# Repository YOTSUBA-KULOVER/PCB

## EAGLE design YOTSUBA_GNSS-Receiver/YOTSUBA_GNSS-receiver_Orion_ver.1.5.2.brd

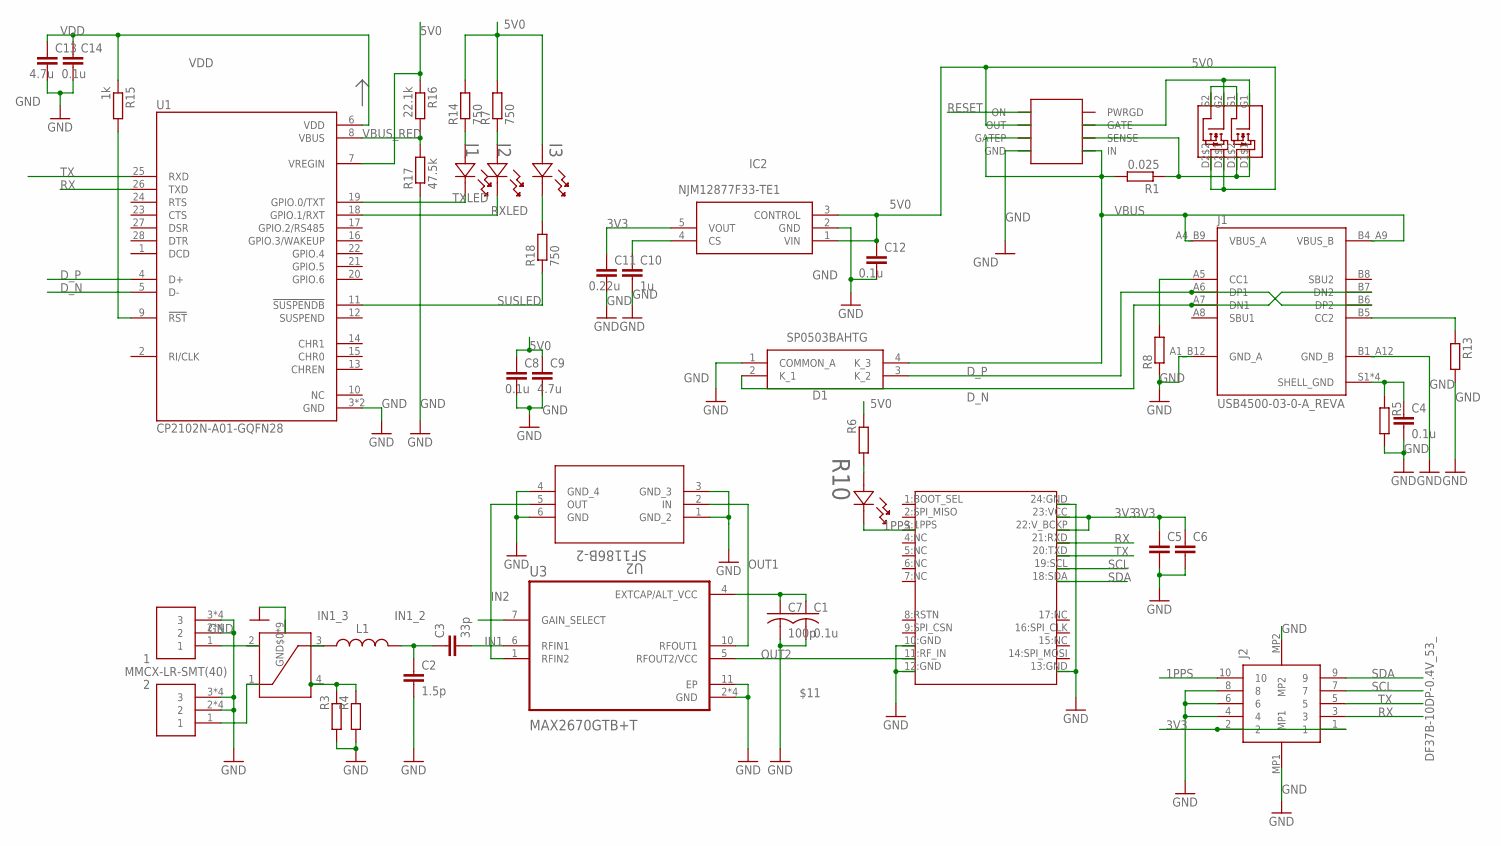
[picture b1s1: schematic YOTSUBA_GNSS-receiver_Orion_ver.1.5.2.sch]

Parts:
1, 2: MMCX-LR-SMT(40)
C1: 0.1u; C1608_OS
C2: 1.5p; C1608
C3: 33p; C1608
C4, C8, C12, C14: 0.1u; C1608
C5, C6: C-EUC1608; C1608
C7: 100p; C1608_OS
C9, C13: 4.7u; C1608
C10: 1u; C1608
C11: 0.22u; C1608
D1: SP0503BAHTG
I1, I2, I3: SML-E12P8WT86; LED_SMLD12_ROM
IC2: NJM12877F33-TE1; SOT95P280X120-5N
J1: USB4500-03-0-A_REVA; GCT_USB4500-03-0-A_REVA
J2: DF37B-10DP-0.4V_53_; DF37B10DP04V53
L1: LQW18AN4N3C00D; INDC1608X100N
R1: 0.025; R0603
R3, R4, R5, R6, R8, R13: R-EU_R0603; R0603
R7, R14, R18: 750; R0603
R10: SML-E12P8WT86; LED_SMLD12_ROM
R15: 1k; R0603
R16: 22.1k; R0603
R17: 47.5k; R0603
U1: CP2102N-A01-GQFN28; QFN50P500X500X80-29N
U2: SF1186B-2; SM3030_MUR
U3: MAX2670GTB+T; DFN300X300X80-11N
U$1: ORION_B16
U$3: HC125.A
U$7: DMG6898LSD; SOIC127P600X150-8N
U$8: LTC4361; SOP65P280X100-8N

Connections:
1PPS: J2.10, R10.1, U$1.3:1PPS
3V3: C5.1, C6.1, C11.1, IC2.5 (VOUT), J2.1, J2.2, U$1.22:V_BCKP, U$1.23:VCC
5V0: C8.1, C9.1, C12.1, I3.2, IC2.1 (VIN), IC2.3 (CONTROL), R6.2, R7.2, R14.2, R16.1, U1.7 (VREGIN), U$7.D2$1, U$7.D2$2, U$8.OUT
$11: C1.1, C7.1, U3.4 (EXTCAP/ALT_VCC)
D_N: D1.2 (K_1), J1.A7 (DN1), J1.B7 (DN2), U1.5 (D-)
D_P: D1.3 (K_2), J1.A6 (DP1), J1.B6 (DP2), U1.4 (D+)
GND: 1.2, 1.3, 1.4 (2), 1.5 (3), 1.P$1 (2), 1.P$2 (2), 1.P$3 (3), 1.P$4 (3), 2.2, 2.3, 2.4 (2), 2.5 (3), 2.P$1 (2), 2.P$2 (2), 2.P$3 (3), 2.P$4 (3), C1.2, C2.2, C4.2, C5.2, C6.2, C7.2, C8.2, C9.2, C10.2, C11.2, C12.2, C13.2, C14.2, D1.1 (COMMON_A), IC2.2 (GND), J1.A1_B12 (GND_A), J1.B1_A12 (GND_B), J2.4, J2.6, J2.8, J2.MP1, J2.MP2, R3.1, R4.1, R5.2, R8.1, R13.2, R17.1, U1.3 (GND), U1.29 (GND), U2.1 (GND_2), U2.3 (GND_3), U2.4 (GND_4), U2.6 (GND), U3.2 (GND), U3.3 (GND), U3.8 (GND), U3.9 (GND), U3.11 (EP), U$1.10:GND, U$1.12:GND, U$1.13:GND, U$1.24:GND, U$3.GND$0 (GND), U$3.GND$1 (GND), U$3.GND$2 (GND), U$3.GND$3 (GND), U$3.GND$4 (GND), U$3.GND$5 (GND), U$3.GND$6 (GND), U$3.GND$7 (GND), U$3.GND$8 (GND), U$8.GND
IN1: C3.2, U3.6 (RFIN1)
IN1_2: C2.1, C3.1, L1.2
IN1_3: L1.1, U$3.3
IN2: U2.5 (OUT), U3.1 (RFIN2)
unnamed: 1.1, U$3.2
unnamed: 2.1, U$3.1
unnamed: I3.1, R18.2
unnamed: C10.1, IC2.4 (CS)
unnamed: I2.2, R7.1
unnamed: C4.1, J1.S1 (SHELL_GND), J1.S2 (SHELL_GND), J1.S3 (SHELL_GND), J1.S4 (SHELL_GND), R5.1
unnamed: I1.2, R14.1
unnamed: R3.2, R4.2, U$3.4
unnamed: R6.1, R10.2
unnamed: U$7.S1, U$7.S2
unnamed: R1.1, U$7.D1$1, U$7.D1$2, U$8.SENSE
unnamed: J1.B5 (CC2), R13.1
unnamed: U$7.G1, U$7.G2, U$8.GATE
unnamed: J1.A5 (CC1), R8.2
unnamed: R15.2, U1.9 (!RST)
OUT1: U2.2 (IN), U3.10 (RFOUT1)
OUT2: U3.5 (RFOUT2/VCC), U$1.11:RF_IN
RESET: U$8.ON
RX: J2.3, U1.26 (TXD), U$1.21:RXD
RXLED: I2.1, U1.18 (GPIO.1/RXT)
SCL: J2.7, U$1.19:SCL
SDA: J2.9, U$1.18:SDA
SUSLED: R18.1, U1.11 (!SUSPENDB)
TX: J2.5, U1.25 (RXD), U$1.20:TXD
TXLED: I1.1, U1.19 (GPIO.0/TXT)
VBUS: D1.4 (K_3), J1.A4_B9 (VBUS_A), J1.B4_A9 (VBUS_B), R1.2, U$8.GATEP, U$8.IN
VBUS_RED: R16.2, R17.2, U1.8 (VBUS)
VDD: C13.1, C14.1, R15.1, U1.6 (VDD)

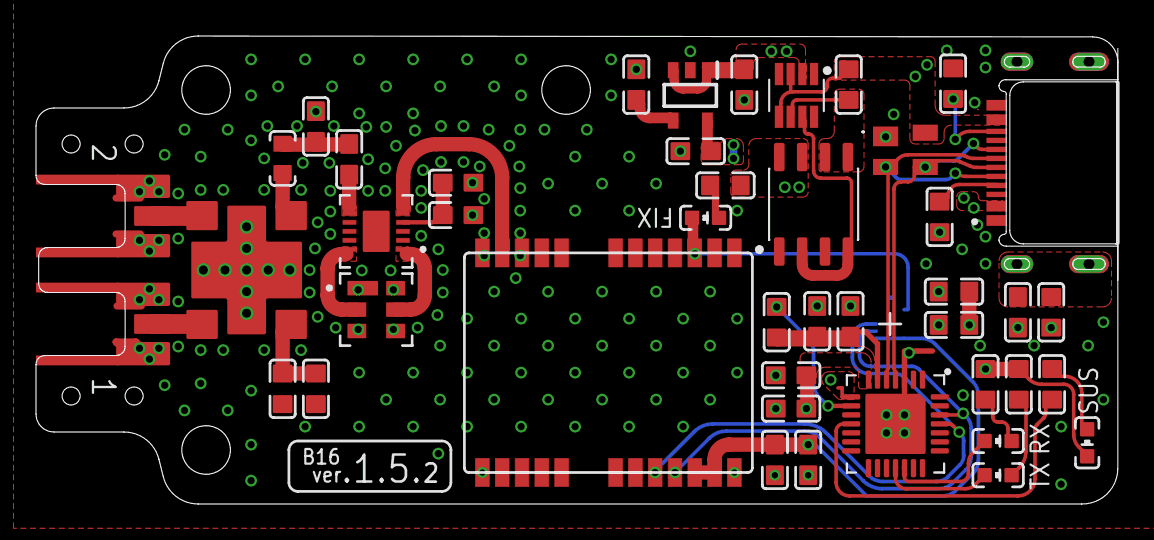
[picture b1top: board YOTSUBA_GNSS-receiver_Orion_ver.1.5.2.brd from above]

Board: 4 copper layers, 60.1 x 26.0 mm, 45 parts (1 on the bottom side), 38 nets.

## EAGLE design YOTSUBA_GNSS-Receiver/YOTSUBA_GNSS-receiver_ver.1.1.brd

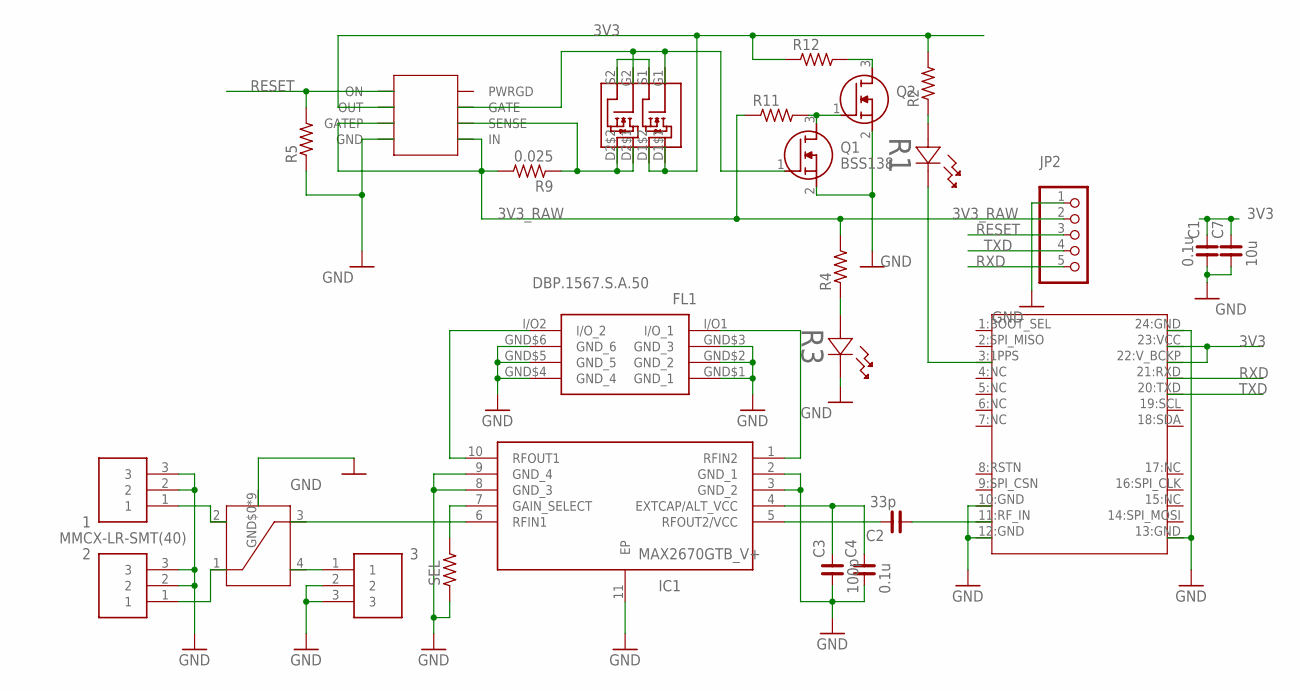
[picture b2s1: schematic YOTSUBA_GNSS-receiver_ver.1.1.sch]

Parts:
1, 2, 3: MMCX-LR-SMT(40)
C1, C4: 0.1u; C0603
C2: 33p; C0603
C3: 100p; C0603
C7: 10u; C0603
FL1: DBP.1567.S.A.50; DBP1567SA50
IC1: MAX2670GTB_V+; SON50P300X300X80-11N
JP2: PINHD-1X5; 1X05
Q1, Q2: BSS138; SOT95P240X120-3N
R1, R3: SML-E12P8WT86; LED_SMLD12_ROM
R2, R4, R5, R11, R12: R_0603; R0603
R9: 0.025; R0603
SEL: R_0603; R0603
U$1: ORION_B16
U$3: HC125.A
U$7: DMG6898LSD; SOIC127P600X150-8N
U$8: LTC4361; SOP65P280X100-8N

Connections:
3V3: C1.2, C7.2, R2.2, R12.1, U$1.22:V_BCKP, U$1.23:VCC, U$7.D1$1, U$7.D1$2, U$8.OUT
3V3_RAW: JP2.2, R4.2, R9.2, R11.1, U$8.GATEP, U$8.IN
GND: 1.2, 1.3, 2.2, 2.3, 3.2, 3.3, C1.1, C3.1, C4.1, C7.1, FL1.GND$1 (GND_1), FL1.GND$2 (GND_2), FL1.GND$3 (GND_3), FL1.GND$4 (GND_4), FL1.GND$5 (GND_5), FL1.GND$6 (GND_6), IC1.2 (GND_1), IC1.3 (GND_2), IC1.8 (GND_3), IC1.9 (GND_4), IC1.11 (EP), JP2.1, Q1.2 (S), Q2.2 (S), R3.1, R5.1, SEL.1, U$1.10:GND, U$1.12:GND, U$1.13:GND, U$1.24:GND, U$3.GND$0 (GND), U$3.GND$1 (GND), U$3.GND$2 (GND), U$3.GND$3 (GND), U$3.GND$4 (GND), U$3.GND$5 (GND), U$3.GND$6 (GND), U$3.GND$7 (GND), U$3.GND$8 (GND), U$8.GND
unnamed: 1.1, U$3.2
unnamed: 2.1, U$3.1
unnamed: IC1.6 (RFIN1), U$3.3
unnamed: R1.1, U$1.3:1PPS
unnamed: R1.2, R2.1
unnamed: 3.1, U$3.4
unnamed: IC1.7 (GAIN_SELECT), SEL.2
unnamed: FL1.I/O2 (I/O_2), IC1.10 (RFOUT1)
unnamed: FL1.I/O1 (I/O_1), IC1.1 (RFIN2)
unnamed: C3.2, C4.2, IC1.4 (EXTCAP/ALT_VCC)
unnamed: C2.2, IC1.5 (RFOUT2/VCC)
unnamed: C2.1, U$1.11:RF_IN
unnamed: R3.2, R4.1
unnamed: U$7.S1, U$7.S2
unnamed: R9.1, U$7.D2$1, U$7.D2$2, U$8.SENSE
unnamed: Q1.1 (G), U$7.G1, U$7.G2, U$8.GATE
unnamed: Q1.3 (D), Q2.1 (G), R11.2
unnamed: Q2.3 (D), R12.2
RESET: JP2.3, R5.2, U$8.ON
RXD: JP2.5, U$1.21:RXD
TXD: JP2.4, U$1.20:TXD

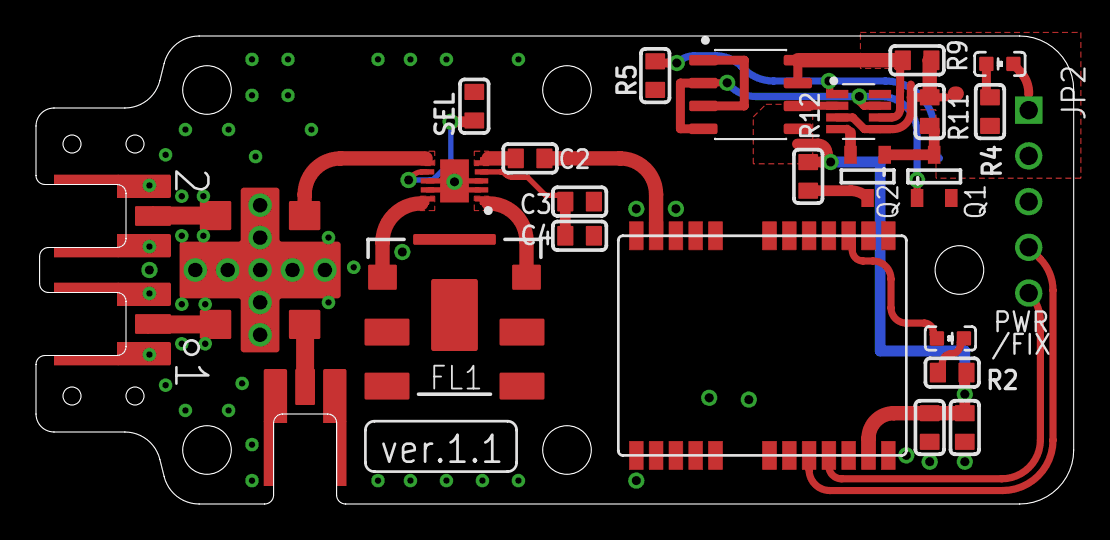
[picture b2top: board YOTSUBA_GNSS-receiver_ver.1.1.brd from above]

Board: 2 copper layers, 57.6 x 26.0 mm, 26 parts (0 on the bottom side), 24 nets.

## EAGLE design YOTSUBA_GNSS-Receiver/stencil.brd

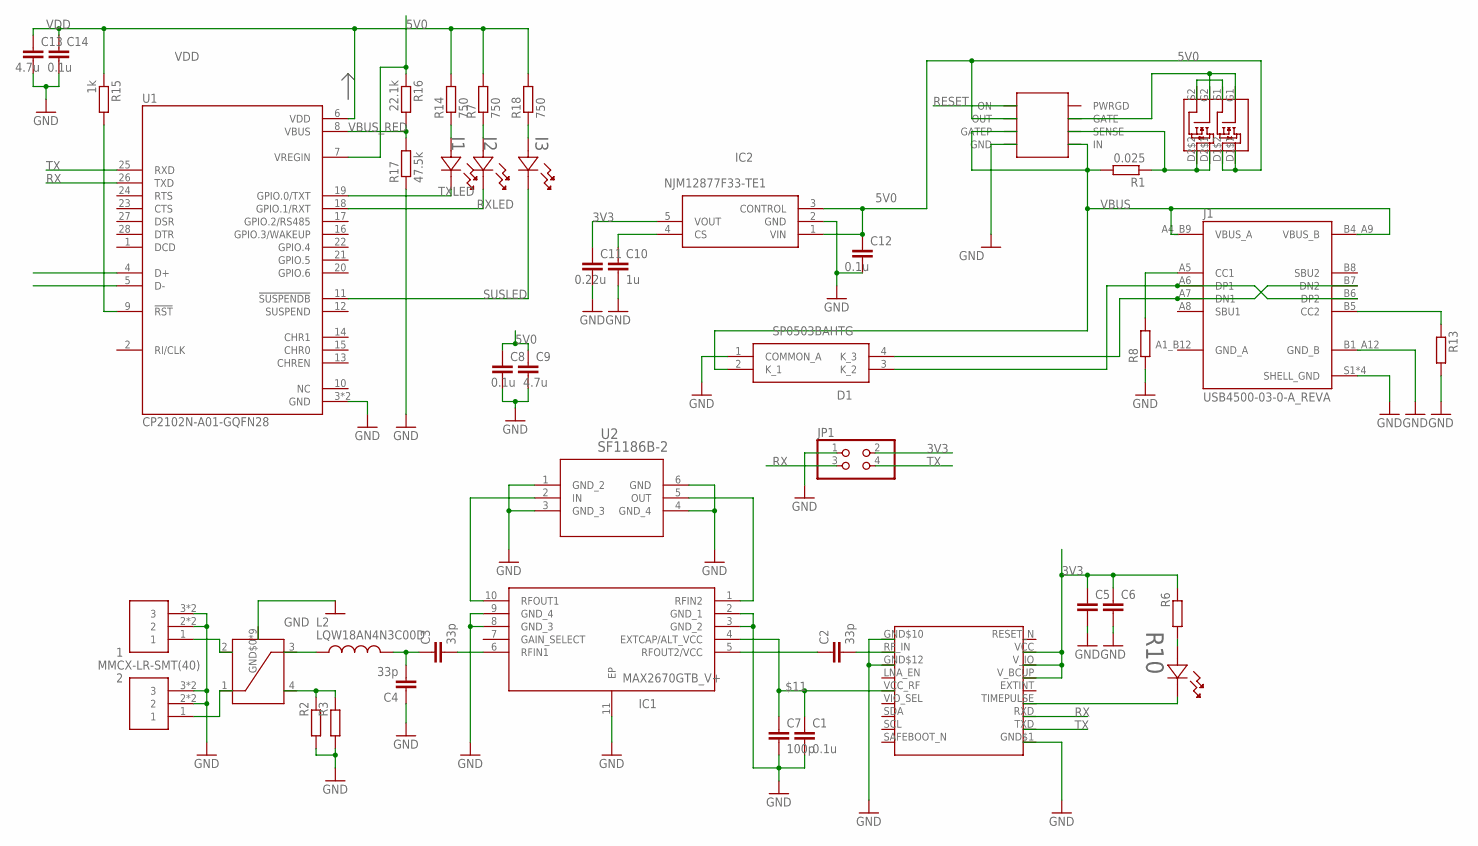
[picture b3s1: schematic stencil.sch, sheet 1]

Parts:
1, 2: MMCX-LR-SMT(40)
C1, C8, C12, C14: 0.1u; C1608
C2, C3, C4: 33p; C1608
C5, C6: C-EUC1608; C1608
C7: 100p; C1608
C9, C13: 4.7u; C1608
C10: 1u; C1608
C11: 0.22u; C1608
D1: SP0503BAHTG
I1, I2, I3: SML-E12P8WT86; LED_SMLD12_ROM
IC1: MAX2670GTB_V+; SON50P300X300X80-11N
IC2: NJM12877F33-TE1; SOT95P280X120-5N
J1: USB4500-03-0-A_REVA; GCT_USB4500-03-0-A_REVA
JP1: PINHD-2X2; 2X02
L2: LQW18AN4N3C00D; INDC1608X100N
R1: 0.025; R0603
R2, R3, R6, R8, R13: R-EU_R0603; R0603
R7, R14, R18: 750; R0603
R10: SML-E12P8WT86; LED_SMLD12_ROM
R15: 1k; R0603
R16: 22.1k; R0603
R17: 47.5k; R0603
U1: CP2102N-A01-GQFN28; QFN50P500X500X80-29N
U2: SF1186B-2; SM3030_MUR
U$1: MAX_M10S; MAX-M10S
U$3: HC125.A
U$7: DMG6898LSD; SOIC127P600X150-8N
U$8: LTC4361; SOP65P280X100-8N

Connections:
3V3: C5.1, C6.1, C11.1, IC2.5 (VOUT), JP1.2, R6.2, U$1.VCC, U$1.V_BCUP (V_BCKP), U$1.V_IO; also elsewhere on the board
5V0: C8.1, C9.1, C12.1, IC2.1 (VIN), IC2.3 (CONTROL), R16.1, U1.7 (VREGIN), U$7.D1$1, U$7.D1$2, U$8.OUT; also elsewhere on the board
$11: C1.1, C7.1, IC1.4 (EXTCAP/ALT_VCC), U$1.VCC_RF
D+: D1.3 (K_2), J1.A6 (DP1), J1.B6 (DP2), U1.4 (D+)
D-: D1.4 (K_3), J1.A7 (DN1), J1.B7 (DN2), U1.5 (D-)
GND: 1.2, 1.3, 1.4 (2), 1.5 (3), 2.2, 2.3, 2.4 (2), 2.5 (3), C1.2, C4.1, C5.2, C6.2, C7.2, C8.2, C9.2, C10.2, C11.2, C12.2, C13.2, C14.2, D1.1 (COMMON_A), IC1.2 (GND_1), IC1.3 (GND_2), IC1.8 (GND_3), IC1.9 (GND_4), IC1.11 (EP), IC2.2 (GND), J1.A1_B12 (GND_A), J1.B1_A12 (GND_B), J1.S1 (SHELL_GND), J1.S2 (SHELL_GND), J1.S3 (SHELL_GND), J1.S4 (SHELL_GND), JP1.1, R2.1, R3.1, R8.1, R13.2, R17.1, U1.3 (GND), U1.29 (GND), U2.1 (GND_2), U2.3 (GND_3), U2.4 (GND_4), U2.6 (GND), U$1.GND$1, U$1.GND$10, U$1.GND$12, U$3.GND$0 (GND), U$3.GND$1 (GND), U$3.GND$2 (GND), U$3.GND$3 (GND), U$3.GND$4 (GND), U$3.GND$5 (GND), U$3.GND$6 (GND), U$3.GND$7 (GND), U$3.GND$8 (GND), U$8.GND; also elsewhere on the board
unnamed: 1.1, U$3.2
unnamed: 2.1, U$3.1
unnamed: C10.1, IC2.4 (CS)
unnamed: I2.2, R7.1
unnamed: R2.2, R3.2, U$3.4
unnamed: L2.1, U$3.3
unnamed: IC1.10 (RFOUT1), U2.2 (IN)
unnamed: IC1.1 (RFIN2), U2.5 (OUT)
unnamed: C3.2, IC1.6 (RFIN1)
unnamed: C2.1, IC1.5 (RFOUT2/VCC)
unnamed: C2.2, U$1.RF_IN
unnamed: I1.2, R14.1
unnamed: R10.1, U$1.TIMEPULSE
unnamed: R6.1, R10.2
unnamed: I3.2, R18.1
unnamed: C3.1, C4.2, L2.2
unnamed: U$7.S1, U$7.S2
unnamed: R1.1, U$7.D2$1, U$7.D2$2, U$8.SENSE
unnamed: J1.B5 (CC2), R13.1
unnamed: U$7.G1, U$7.G2, U$8.GATE
unnamed: J1.A5 (CC1), R8.2
unnamed: R15.2, U1.9 (!RST)
RESET: U$8.ON
RX: JP1.3, U1.26 (TXD), U$1.RXD; also elsewhere on the board
RXLED: I2.1, U1.18 (GPIO.1/RXT)
SUSLED: I3.1, U1.11 (!SUSPENDB)
TX: JP1.4, U1.25 (RXD), U$1.TXD; also elsewhere on the board
TXLED: I1.1, U1.19 (GPIO.0/TXT)
VBUS: D1.2 (K_1), J1.A4_B9 (VBUS_A), J1.B4_A9 (VBUS_B), R1.2, U$8.GATEP, U$8.IN
VBUS_RED: R16.2, R17.2, U1.8 (VBUS)
VDD: C13.1, C14.1, R7.2, R14.2, R15.1, R18.2, U1.6 (VDD)

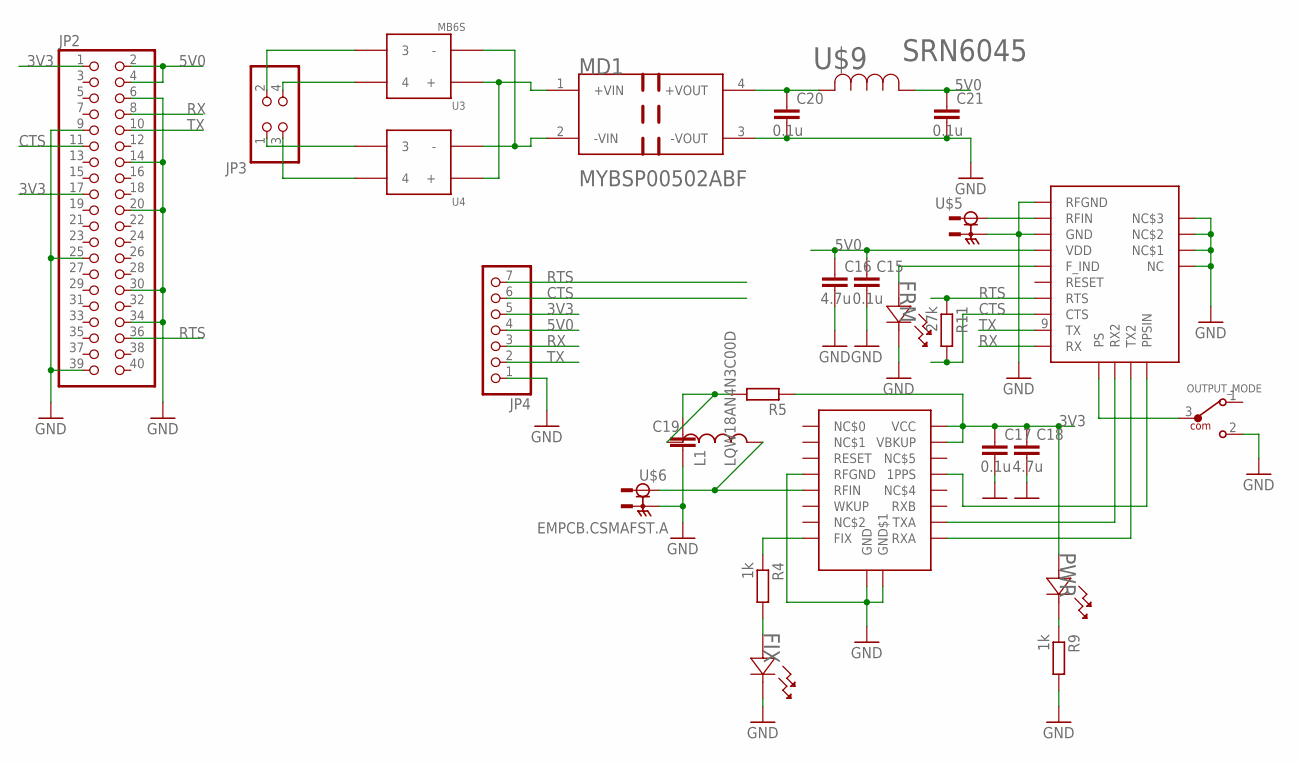
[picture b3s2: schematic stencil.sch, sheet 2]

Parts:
C15, C17, C20, C21: 0.1u; C1608
C16, C18: 4.7u; C1608
C19: C-EUC1608; C1608
FIX: SML-E12P8WT86; LED_SMLD12_ROM
FRM: SML-E12P8WT86; LED_SMLD12_ROM
JP2: PINHD-2X20; 2X20
JP3: PINHD-2X2; 2X02
JP4: PINHD-1X7/90; 1X07/90
L1: LQW18AN4N3C00D; INDC1608X100N
MD1: MURATA_MYBSP00502ABFMURATA_MYBSP00502ABF_0_0; MURATA_MYBSP00502ABF_0
OUTPUT_MODE: 450405020524
PWR: SML-E12P8WT86; LED_SMLD12_ROM
R4, R9: 1k; R0603
R5: R-EU_R0603; R0603
R11: 27k; R0603_NOSILK
U3, U4: MB6S; SOIC245P670X270-4N
U$2: GNS5894T; GNS5XXX
U$4: GNS3303
U$5, U$6: EMPCB.CSMAFST.A
U$9: SRN6045; IND_BOURNS_SRN6045

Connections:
3V3: C17.1, C18.1, JP2.1, JP2.17, JP4.5, PWR.2, R5.1, U$4.15 (VBKUP), U$4.16 (VCC); also elsewhere on the board
5V0: C15.1, C16.1, C21.1, JP2.2, JP2.4, JP4.4, U$2.4 (VDD), U$9.1; also elsewhere on the board
CTS: JP2.11, JP4.6, R11.2, U$2.8 (CTS)
GND: C15.2, C16.2, C17.2, C18.2, C19.2, C20.2, C21.2, FIX.1, FRM.1, JP2.6, JP2.9, JP2.14, JP2.20, JP2.25, JP2.30, JP2.34, JP2.39, JP4.1, MD1.3 (-VOUT), OUTPUT_MODE.2 (3), R9.2, U$2.1 (RFGND), U$2.3 (GND), U$2.15 (NC), U$2.16 (NC$1), U$2.17 (NC$2), U$2.18 (NC$3), U$4.4 (RFGND), U$4.E1 (GND), U$4.E2 (GND$1), U$5.GND$0 (2), U$5.GND$1 (2), U$5.GND$2 (2), U$5.GND$3 (2), U$6.GND$0 (2), U$6.GND$1 (2), U$6.GND$2 (2), U$6.GND$3 (2); also elsewhere on the board
unnamed: FRM.2, U$2.5 (F_IND)
unnamed: U$2.12 (RX2), U$4.10 (TXA)
unnamed: U$2.13 (TX2), U$4.9 (RXA)
unnamed: U$2.14 (PPSIN), U$4.13 (1PPS)
unnamed: R4.1, U$4.8 (FIX)
unnamed: FIX.2, R4.2
unnamed: C19.1, L1.1, R5.2
unnamed: OUTPUT_MODE.3 (2), U$2.11 (PS)
unnamed: PWR.1, R9.1
unnamed: JP3.4, U3.4
unnamed: JP3.2, U3.3
unnamed: JP3.3, U4.4
unnamed: JP3.1, U4.3
unnamed: MD1.2 (-VIN), U3.2 (-), U4.2 (-)
unnamed: MD1.1 (+VIN), U3.1 (+), U4.1 (+)
unnamed: C20.1, MD1.4 (+VOUT), U$9.2
RF1: L1.2, U$4.5 (RFIN), U$6.RF (1)
RF2: U$2.2 (RFIN), U$5.RF (1)
RTS: JP2.36, JP4.7, R11.1, U$2.7 (RTS)
RX: JP2.8, JP4.3, U$2.10 (RX); also elsewhere on the board
TX: JP2.10, JP4.2, U$2.9 (TX); also elsewhere on the board

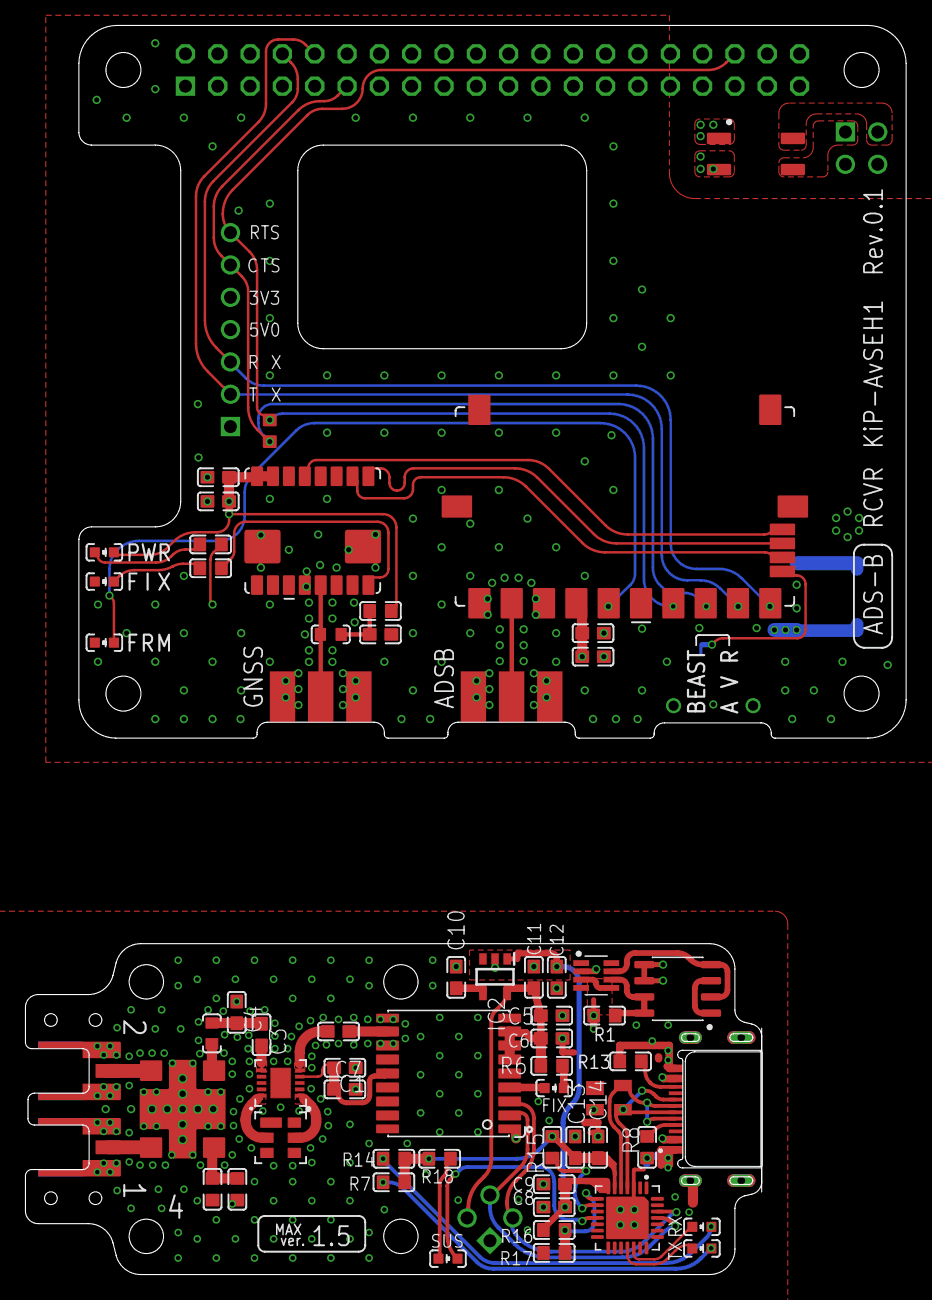
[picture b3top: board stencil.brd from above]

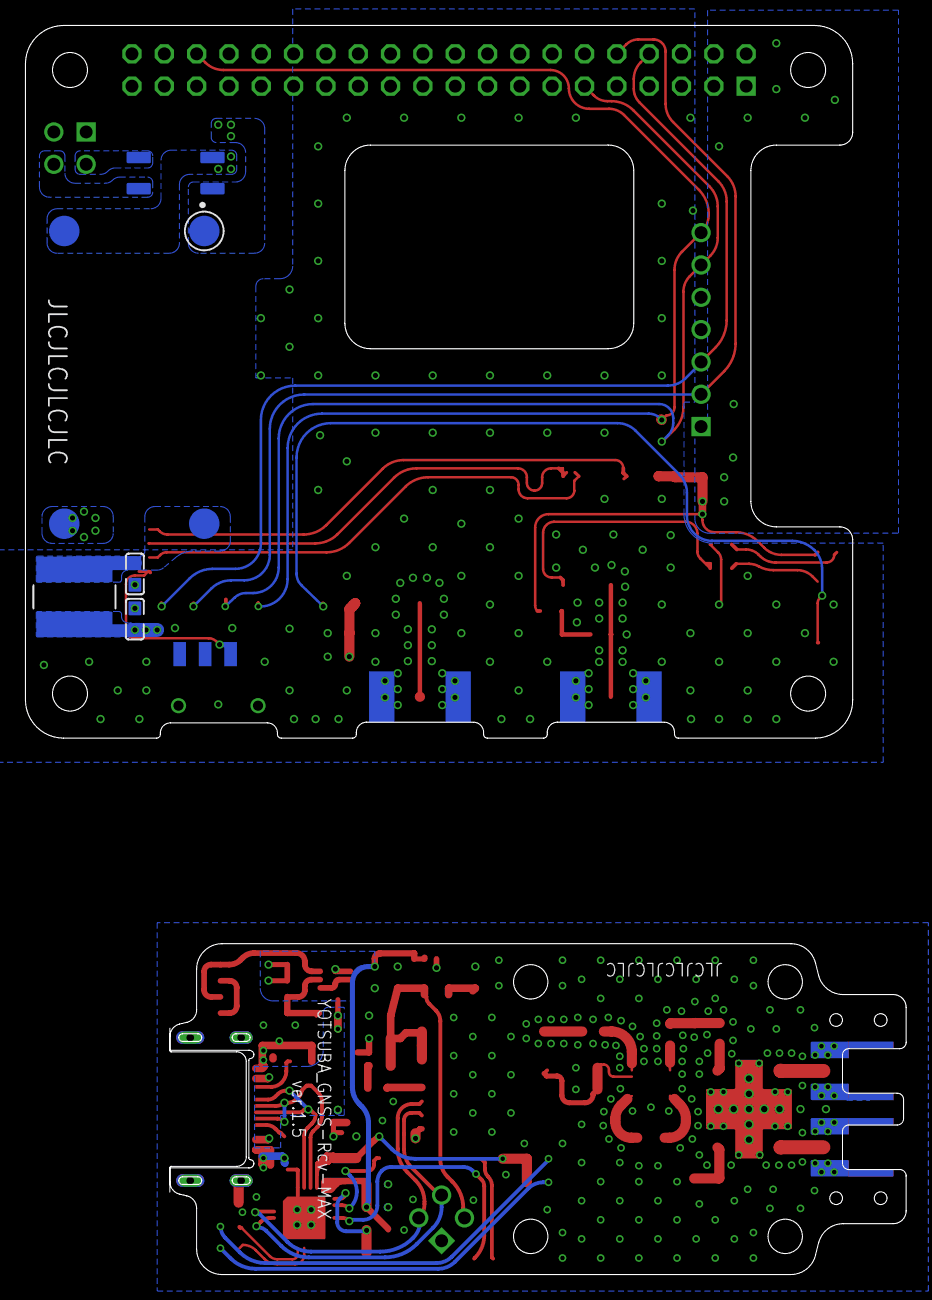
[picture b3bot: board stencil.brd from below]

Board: 2 copper layers, 69.2 x 98.2 mm, 71 parts (7 on the bottom side), 56 nets.

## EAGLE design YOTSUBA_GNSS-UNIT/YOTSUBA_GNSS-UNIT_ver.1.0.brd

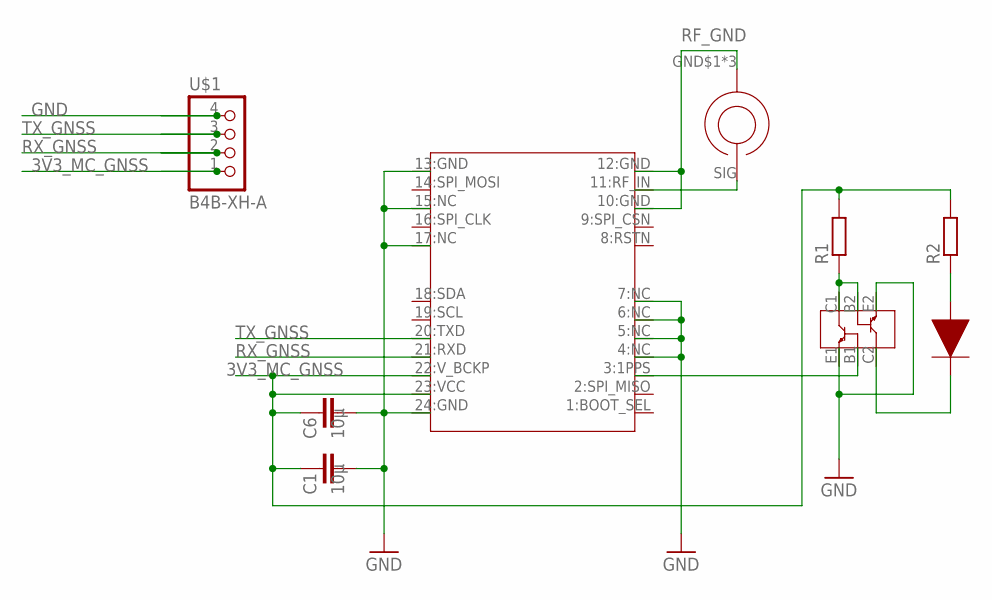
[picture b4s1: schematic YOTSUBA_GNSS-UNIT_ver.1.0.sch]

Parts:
C1, C6: 10μ; C2012
ON/1PPS: LED_1608
R1, R2: R-EU_M2012; M2012
U$1: B4B-XH-A
U$2: ORION_B16
U$3: HN1C01FU; SOT65P210X100-6N
U$5: U.FL-R

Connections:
3V3_MC_GNSS: C1.1, C6.1, R1.2, R2.2, U$1.1, U$2.22:V_BCKP, U$2.23:VCC
GND: C1.2, C6.2, U$1.4, U$2.4:NC, U$2.5:NC, U$2.6:NC, U$2.7:NC, U$2.13:GND, U$2.15:NC, U$2.17:NC, U$2.24:GND, U$3.E1, U$3.E2
unnamed: ON/1PPS.A, R2.1
unnamed: ON/1PPS.C, U$3.C2
unnamed: U$2.3:1PPS, U$3.B1
unnamed: R1.1, U$3.B2, U$3.C1
unnamed: U$2.11:RF_IN, U$5.SIG
RF_GND: U$2.10:GND, U$2.12:GND, U$5.GND$1 (GND), U$5.GND$2 (GND), U$5.GND$3 (GND)
RX_GNSS: U$1.2, U$2.21:RXD
TX_GNSS: U$1.3, U$2.20:TXD

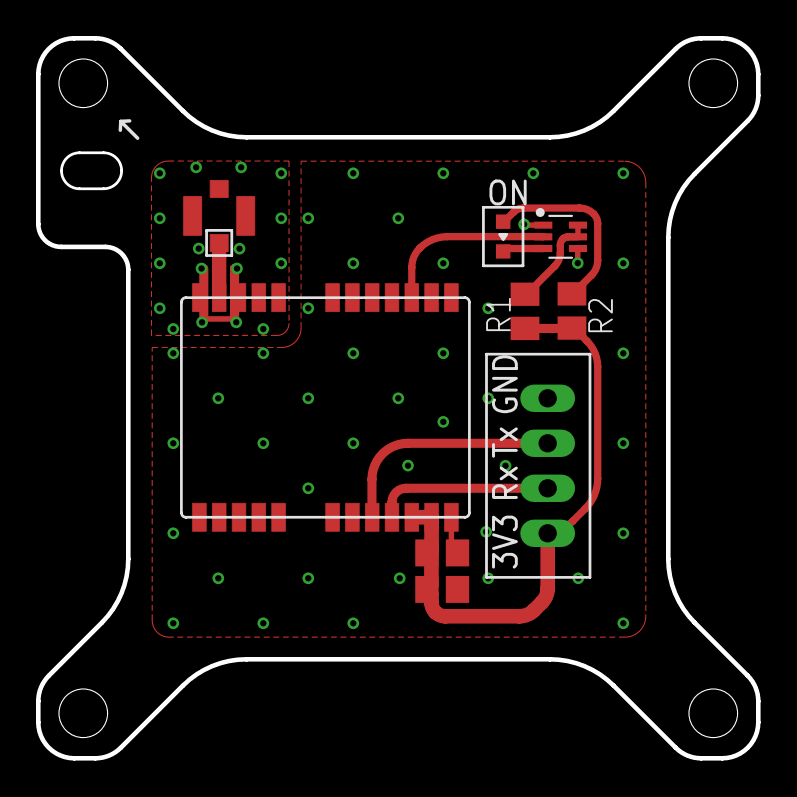
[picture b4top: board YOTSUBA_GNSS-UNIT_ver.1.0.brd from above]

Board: 2 copper layers, 40.0 x 40.0 mm, 9 parts (0 on the bottom side), 10 nets.

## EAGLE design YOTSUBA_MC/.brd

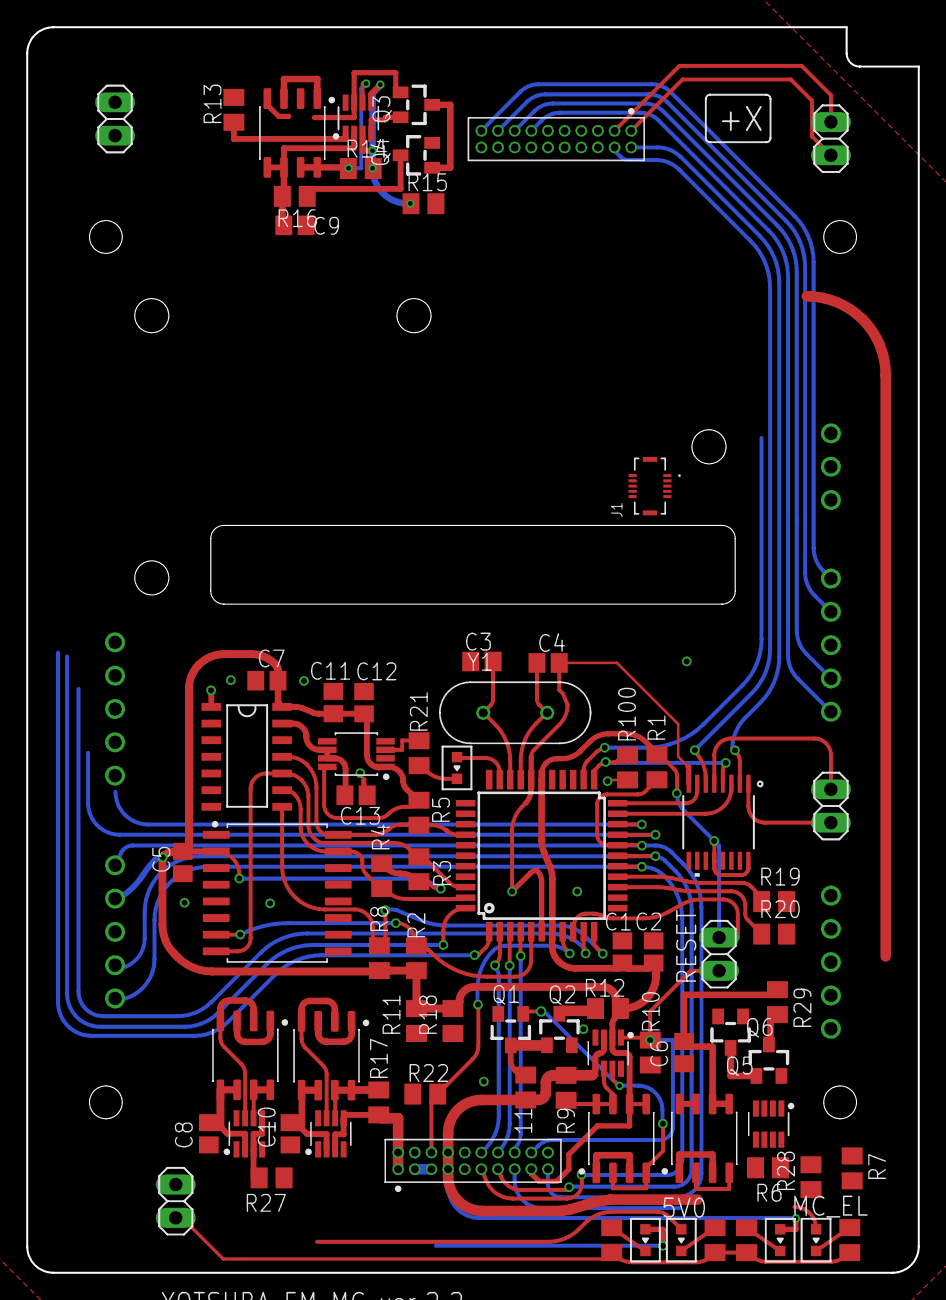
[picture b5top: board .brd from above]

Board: 2 copper layers, 68.0 x 95.0 mm, 84 parts (0 on the bottom side), 76 nets.

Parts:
11: M2012
C1, C2, C3, C4, C5, C6, C7, C8, C9, C10, C11, C12, C13: 10μ; C2012
COM_MAG: 1X05
J1: DF37NB-10DS-0.4V(51); HRS_DF37NB-10DS-0.4V(51)
JP1, JP4: 1X02
MAG_PWR: 1X03
PANEL: 1X05
PROGRAM: 1X05
Q1, Q2, Q3, Q4, Q5, Q6: BSS138; SOT23
R1, R2, R3, R4, R5, R6, R7, R8, R10, R11, R12, R13, R14, R15, R16, R17, R18, R19, R20, R21, R22, R23, R24, R25, R26, R27, R28, R29: M2012
R9: 0.025; M2012
R100: 100k; M2012
RPI: 1X05
U1: MAX4702EUE+; 21-0066J_16
U2: PIC16F877PT; TQFP44
U$1: MT25QL512_16SOP2; SOIC127P1032X265-16N
U$2, U$7, U$9, U$10, U$13: DMG6898LSD; SOIC127P600X150-8N
U$3, U$8, U$11, U$12, U$14: LTC4361; SOP65P280X100-8N
U$6: MCP3204_S
U$16, U$20, U$26: 1X02
U$17, U$22: M50-3001045
U$18, U$21, U$23, U$24, U$25: LED_1608
U$19: ADR35XX; SOP65P490X110-8N
Y1: HC-49/U-S16000000ABJB; XTAL_HC49P488W43L1150T466H350

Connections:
3V3: 11.1, MAG_PWR.1, R6.2, R9.2, R14.2, R15.1, R28.1, U$3.GATEP, U$3.IN, U$8.GATEP, U$8.IN, U$11.GATEP, U$11.IN, U$17.7, U$17.8, U$23.A
3V3_MAG: C6.2, R29.1, U$2.D1$1, U$2.D1$2, U$3.OUT
3V3_MC_EL: C1.1, C2.1, C5.2, C7.2, C11.2, C12.2, JP4.1, PROGRAM.2, R1.2, R2.2, R3.2, R4.2, R5.2, R8.1, R11.2, R12.1, R18.2, U1.12, U1.16, U2.7, U2.28, U$1.VCC, U$6.VDD, U$7.D1$1, U$7.D1$2, U$8.OUT, U$17.17, U$19.ENABLE, U$19.VIN, U$21.A
3V3_MC_GNSS: C9.2, R16.1, U$10.D1$1, U$10.D1$2, U$11.OUT
5V0: R17.2, U$14.GATEP, U$14.IN, U$17.1, U$17.2, U$25.A
5V0_MC_RPI: C10.2, RPI.1, U$13.D1$1, U$13.D1$2, U$14.OUT, U$24.A
7V0: R27.2, U$12.GATEP, U$12.IN, U$17.3, U$17.5
7V0_MAG: C8.2, MAG_PWR.3, U$9.D1$1, U$9.D1$2, U$12.OUT
CS_ADC: R8.2, U2.11, U$6.CS
GND: C1.2, C2.2, C3.2, C4.2, C5.1, C6.1, C7.1, C8.1, C9.1, C10.1, C11.1, C12.1, C13.2, COM_MAG.3, JP1.2, MAG_PWR.2, PANEL.3, PROGRAM.3, Q1.2, Q2.2, Q3.2, Q4.2, Q5.2, Q6.2, R7.2, R10.2, R13.2, R21.1, R22.1, R100.1, RPI.3, U1.8, U2.6, U2.29, U$1.VSS, U$3.GND, U$6.AGND, U$6.DGND, U$8.GND, U$11.GND, U$12.GND, U$12.ON, U$14.GND, U$14.ON, U$17.4, U$17.9, U$17.10, U$19.GND_FORCE, U$19.GND_SENSE, U$22.5, U$22.6, U$22.7, U$22.8, U$22.9, U$22.10, U$22.11, U$22.12, U$22.14, U$22.16, U$22.18, U$22.20, U$26.2
INDI: U2.32, U$18.A
INT<<MAG: COM_MAG.2, U2.9
INT<<MAIN: R22.2, U2.8, U$17.6
INT<<RPI: RPI.2, U2.10
INT>>MAIN: U2.4, U$17.16
MCLR_MAG: PANEL.5, U$22.19
MCLR_MC: PROGRAM.1, R1.1, U2.18, U$17.19
MC_SPI_CLK: R5.1, U2.37, U$1.C, U$6.CLK
MC_SPI_MISO: R3.1, U2.42, U$1.DQ1, U$6.DOUT
MC_SPI_MOSI: R4.1, U2.43, U$1.DQ0, U$6.DIN
unnamed: R19.2, R20.2
unnamed: R23.2, U$21.C
unnamed: C3.1, U2.31, Y1.1
unnamed: R24.2, U$23.C
unnamed: C4.1, U2.30, Y1.2
unnamed: R25.2, U$24.C
unnamed: R26.2, U$25.C
unnamed: R2.1, U2.5, U$1.S#
unnamed: JP1.1, R23.1, R24.1, R25.1, R26.1
unnamed: U$2.S1, U$2.S2
unnamed: R6.1, U$2.D2$1, U$2.D2$2, U$3.SENSE
unnamed: Q5.1, U$2.G1, U$2.G2, U$3.GATE
unnamed: Q5.3, Q6.1, R28.2
unnamed: U$9.S1, U$9.S2
unnamed: R21.2, U$18.C
unnamed: R27.1, U$9.D2$1, U$9.D2$2, U$12.SENSE
unnamed: U$9.G1, U$9.G2, U$12.GATE
unnamed: Q6.3, R29.2
unnamed: U$7.S1, U$7.S2
unnamed: R9.1, U$7.D2$1, U$7.D2$2, U$8.SENSE
unnamed: Q1.1, U$7.G1, U$7.G2, U$8.GATE
unnamed: 11.2, Q1.3, Q2.1
unnamed: Q2.3, R12.2
unnamed: U$10.S1, U$10.S2
unnamed: R14.1, U$10.D2$1, U$10.D2$2, U$11.SENSE
unnamed: Q3.1, U$10.G1, U$10.G2, U$11.GATE
unnamed: Q3.3, Q4.1, R15.2
unnamed: Q4.3, R16.2
unnamed: U$13.S1, U$13.S2
unnamed: R17.1, U$13.D2$1, U$13.D2$2, U$14.SENSE
unnamed: U$13.G1, U$13.G2, U$14.GATE
OUT0_ADC: U$6.CH0, U$26.1
PGC_MAG: PANEL.1, U$22.13
PGC_MC: PROGRAM.5, U2.16, U$17.11
PGD_MAG: PANEL.2, U$22.15
PGD_MC: PROGRAM.4, U2.17, U$17.13
RESET_MAG_EXT: COM_MAG.1, R7.1, U$3.ON, U$17.15
RESET_MC_EL: JP4.2, R10.1, U$8.ON, U$17.18
RESET_MC_GNSS: R13.1, U2.24, U$11.ON
RPI_EPS_IO_1: U$20.1, U$22.1
RPI_EPS_IO_2: U$20.2, U$22.3
RX_MC_TX_MAG: COM_MAG.4, R20.1, U2.14
RX_MC_TX_MAIN: R18.1, U2.3, U$17.14
RX_MC_TX_RPI: RPI.4, U2.19
SELECT: R100.2, U1.4, U2.23
TRCLK>>COM: U1.2, U$22.2
TRCLK_MC: U1.3, U2.21
TRCLK_RPI: U1.1, U$16.1
TRDAT>>COM: U1.6, U$22.4
TRDAT_MC: U1.7, U2.22
TRDAT_RPI: U1.5, U$16.2
TX_MC_RX_MAG: COM_MAG.5, R19.1, U2.15
TX_MC_RX_MAIN: R11.1, U2.2, U$17.12
TX_MC_RX_RPI: RPI.5, U2.20
VDD_MAG: PANEL.4, U$22.17
VREF_2V5: C13.1, U$6.VREF, U$19.VOUT_FORCE, U$19.VOUT_SENSE

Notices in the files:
parts and their libraries:
COPYRIGHT: Copyright (C) 2023 Ultra Librarian. All rights reserved.
rc-master_custom: Copyright (C) 2007, Bob Starr
WS-SLSU: Copyright: Würth Elektronik
COPYRIGHT: Copyright (C) 2022 Ultra Librarian. All rights reserved.
